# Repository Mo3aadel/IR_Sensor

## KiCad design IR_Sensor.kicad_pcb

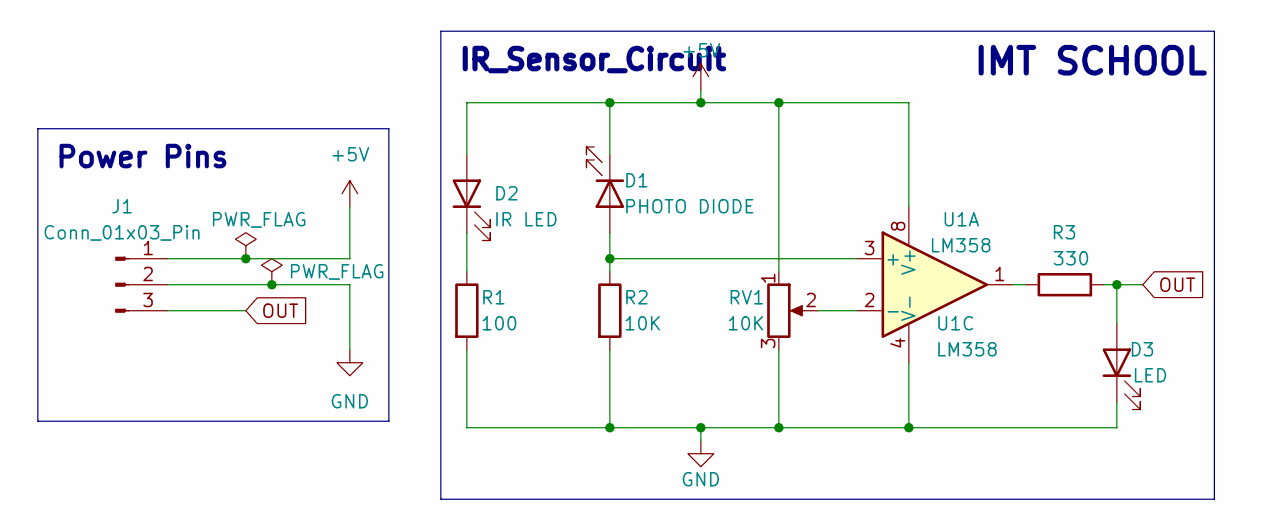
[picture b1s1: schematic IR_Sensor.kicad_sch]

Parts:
D1: PHOTO DIODE; LED_D5.0mm_Horizontal_O3.81mm_Z3.0mm
D2: IR LED; LED_D5.0mm_Horizontal_O3.81mm_Z3.0mm
D3: LED; LED_1206_3216Metric_Pad1.42x1.75mm_HandSolder
J1: Conn_01x03_Pin; PinHeader_1x03_P2.54mm_Horizontal
R1: 100; R_1206_3216Metric_Pad1.30x1.75mm_HandSolder
R2: 10K; R_1206_3216Metric_Pad1.30x1.75mm_HandSolder
R3: 330; R_1206_3216Metric_Pad1.30x1.75mm_HandSolder
RV1: 10K; Potentiometer_Bourns_3314G_Vertical
U1: LM358; DIP-8_W7.62mm_SMDSocket_SmallPads

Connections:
+5V: D1.1 (K), D2.2 (A), J1.1, RV1.1, U1.8 (V+)
GND: D3.1 (K), J1.2, R1.2, R2.2, RV1.3, U1.4 (V-)
unnamed: D1.2 (A), R2.1, U1.3 (+)
unnamed: D2.1 (K), R1.1
unnamed: R3.1, U1.1
unnamed: RV1.2, U1.2 (-)
OUT: D3.2 (A), J1.3, R3.2

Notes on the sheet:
IR_Sensor_Circuit
Power Pins
IMT SCHOOL

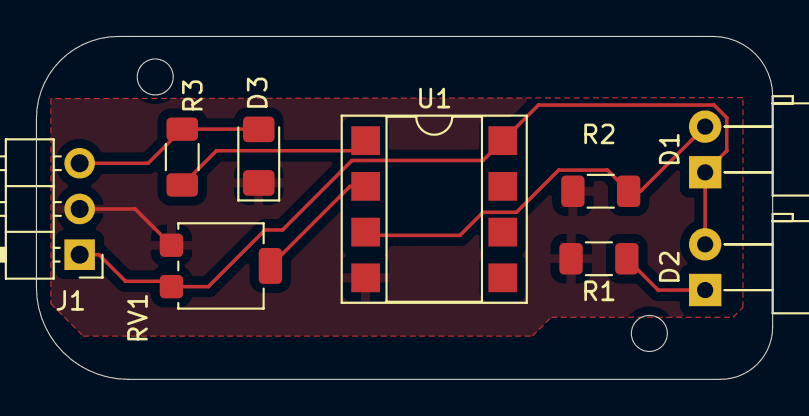
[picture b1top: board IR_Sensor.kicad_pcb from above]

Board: 2 copper layers, 40.9 x 19.0 mm, 9 parts (0 on the bottom side), 7 nets.

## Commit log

2024-12-27 updated the new logo
